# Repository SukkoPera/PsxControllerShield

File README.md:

# PsxControllerShield
PsxControllerShield is an Open Hardware shield for [Arduino](https://www.arduino.cc) that allows it to be interfaced with Sony PlayStation controllers.

### Summary
Interfacing PlayStation controllers with Arduino is easy, since the protocol they use is essentially SPI, but it is a bit tricky at the hardware level, since they are designed to work at 3.6V, while most Arduino work at 5V. A lot of guides out there seem to ignore this fact and say that controllers will work fine even at 5V, but I doubt this will not harm them in the long run. Since overcoming the problem is pretty easy, I designed this shield, which includes level shifters on all data lines and a voltage regulator that will produce much more current than even the most power-greedy controller will need. Just place it on your Arduino, connect the controller and you are good to go!

The shield was designed to be used with [PsxNewLib](https://github.com/SukkoPera/PsxNewLib) on the software side (versions 0.2 and later have a built-in example for that), but it will probably work with other libraries and/or custom code just as well.

The shield also includes three leds that can be freely used by sketches.

### Components and Assembly
Solder all parts in the order you prefer, just keep the controller connector last. This can be found from many Chinese sellers as a spare part. Get one with 90° pins, otherwise the adapter will be pretty awkward to use. The pins will be pretty short, but if you make sure it sits level on the board you should manage to solder it in place, maybe from the top. In order to make the adapter more mechanically solid, you can put some hot glue behind the connector (where the pins are), it won't look pretty but it will do the job.

Note that the controller is powered at 3.3V and the interface signals use the same voltage. Due to the particular circuit used for level shifting (the microcontroller works at 5V), the MOSFETs should really be BSS138.

**NOTE: I recommend using 1k resistors for R1 through R10.** I have checked on a real PsOne and that's the value it uses, so I guess we should do the same. This will be fixed in the next release.

### Compatibility
For the list of supported controllers, please refer to the [PsxNewLib Compatibility List](https://github.com/SukkoPera/PsxNewLib#compatibility-list).

Regarding the supported Arduino boards, this shield should work with all those that work at 5V, such as the *Uno*, *Leonardo* and *Mega*. **It will NOT work with the Due** or other boards that use a 3.3V logic level, and **it will probably destroy them**, so be careful.

If you plan to use the vibration motors you will need to provide them with suitable power, that is 7.6V-9V. This can be done through the barrel jack which should be available on your Arduino board or through the VIN pin. Pay attention **to match the polarity**! Please note that this is untested at the moment (since it is currently not supported by PsxNewLib).

#### Pin Restrictions
The shield uses pin 10 to address the controller and pin 9 for the ACK signal, so these pins cannot be used for any other purpose.

Furthermore, the shield connects the controller data lines to the corresponding pins of the SPI connector (also known as the ICSP connector). Since on some Arduino boards these pins are shared with other digital pins, you won't be able to use them. In particular:
- On the Arduino Uno you cannot use pins 11, 12 and 13.
- On the Arduino Mega you cannot use pins 50, 51 and 52. Pin 53 can be freely used provided that is is kept in OUTPUT mode.

Finally, pins 6, 7 and 8 control the onboard leds (LD3, LD2 and LD1 respectively).

### Releases
If you want to get this board produced, you are recommended to get [the latest release](https://github.com/SukkoPera/PsxControllerShield/releases) rather than the current git version, as the latter might be under development and is not guaranteed to be working.

Every release is accompanied by its Bill Of Materials (BOM) file and any relevant notes about it, which you are recommended to read carefully.

### License
The PsxControllerShield documentation, including the design itself, is copyright &copy; SukkoPera 2020.

PsxControllerShield is Open Hardware licensed under the [CERN OHL v. 1.2](http://ohwr.org/cernohl).

You may redistribute and modify this documentation under the terms of the CERN OHL v.1.2. This documentation is distributed *as is* and WITHOUT ANY EXPRESS OR IMPLIED WARRANTIES whatsoever with respect to its functionality, operability or use, including, without limitation, any implied warranties OF MERCHANTABILITY, SATISFACTORY QUALITY, FITNESS FOR A PARTICULAR PURPOSE or infringement. We expressly disclaim any liability whatsoever for any direct, indirect, consequential, incidental or special damages, including, without limitation, lost revenues, lost profits, losses resulting from business interruption or loss of data, regardless of the form of action or legal theory under which the liability may be asserted, even if advised of the possibility or likelihood of such damages.

A copy of the full license is included in file [LICENSE.pdf](LICENSE.pdf), please refer to it for applicable conditions. In order to properly deal with its terms, please see file [LICENSE_HOWTO.pdf](LICENSE_HOWTO.pdf).

The contact points for information about manufactured Products (see section 4.2) are listed in file [PRODUCT.md](PRODUCT.md).

Any modifications made by Licensees (see section 3.4.b) shall be recorded in file [CHANGES.md](CHANGES.md).

The Documentation Location of the original project is https://github.com/SukkoPera/PsxControllerShield/.

### Support the Project
Since the project is open you are free to get the PCBs made by your preferred manufacturer, however in case you want to support the development, you can order them from PCBWay through this link:

You get my gratitude and cheap, professionally-made and good quality PCBs, I get some credit that will help with this and [other projects](https://www.pcbway.com/project/member/shareproject/?bmbid=41100). You won't even have to worry about the various PCB options, it's all pre-configured for you!

Also, if you still have to register to that site, [you can use this link](https://www.pcbway.com/setinvite.aspx?inviteid=41100) to get some bonus initial credit (and yield me some more).

Again, if you want to use another manufacturer, feel free to, don't feel obligated :). But then you can buy me a coffee if you want:

### Get Help
If you need help or have questions, you can join [the official Telegram group](https://t.me/joinchat/HUHdWBC9J9JnYIrvTYfZmg).

### Thanks
- CuriousInventor for information about the [PlayStation controller protocol](http://store.curiousinventor.com/guides/PS2)
- Nicholas Parks Young for his [Arduino Shield schematic and footprint library for KiCad](https://github.com/Alarm-Siren/arduino-kicad-library)
- Sarang Dumbre for his [3D model of the PlayStation connector](https://grabcad.com/library/ps-connector-female-1)

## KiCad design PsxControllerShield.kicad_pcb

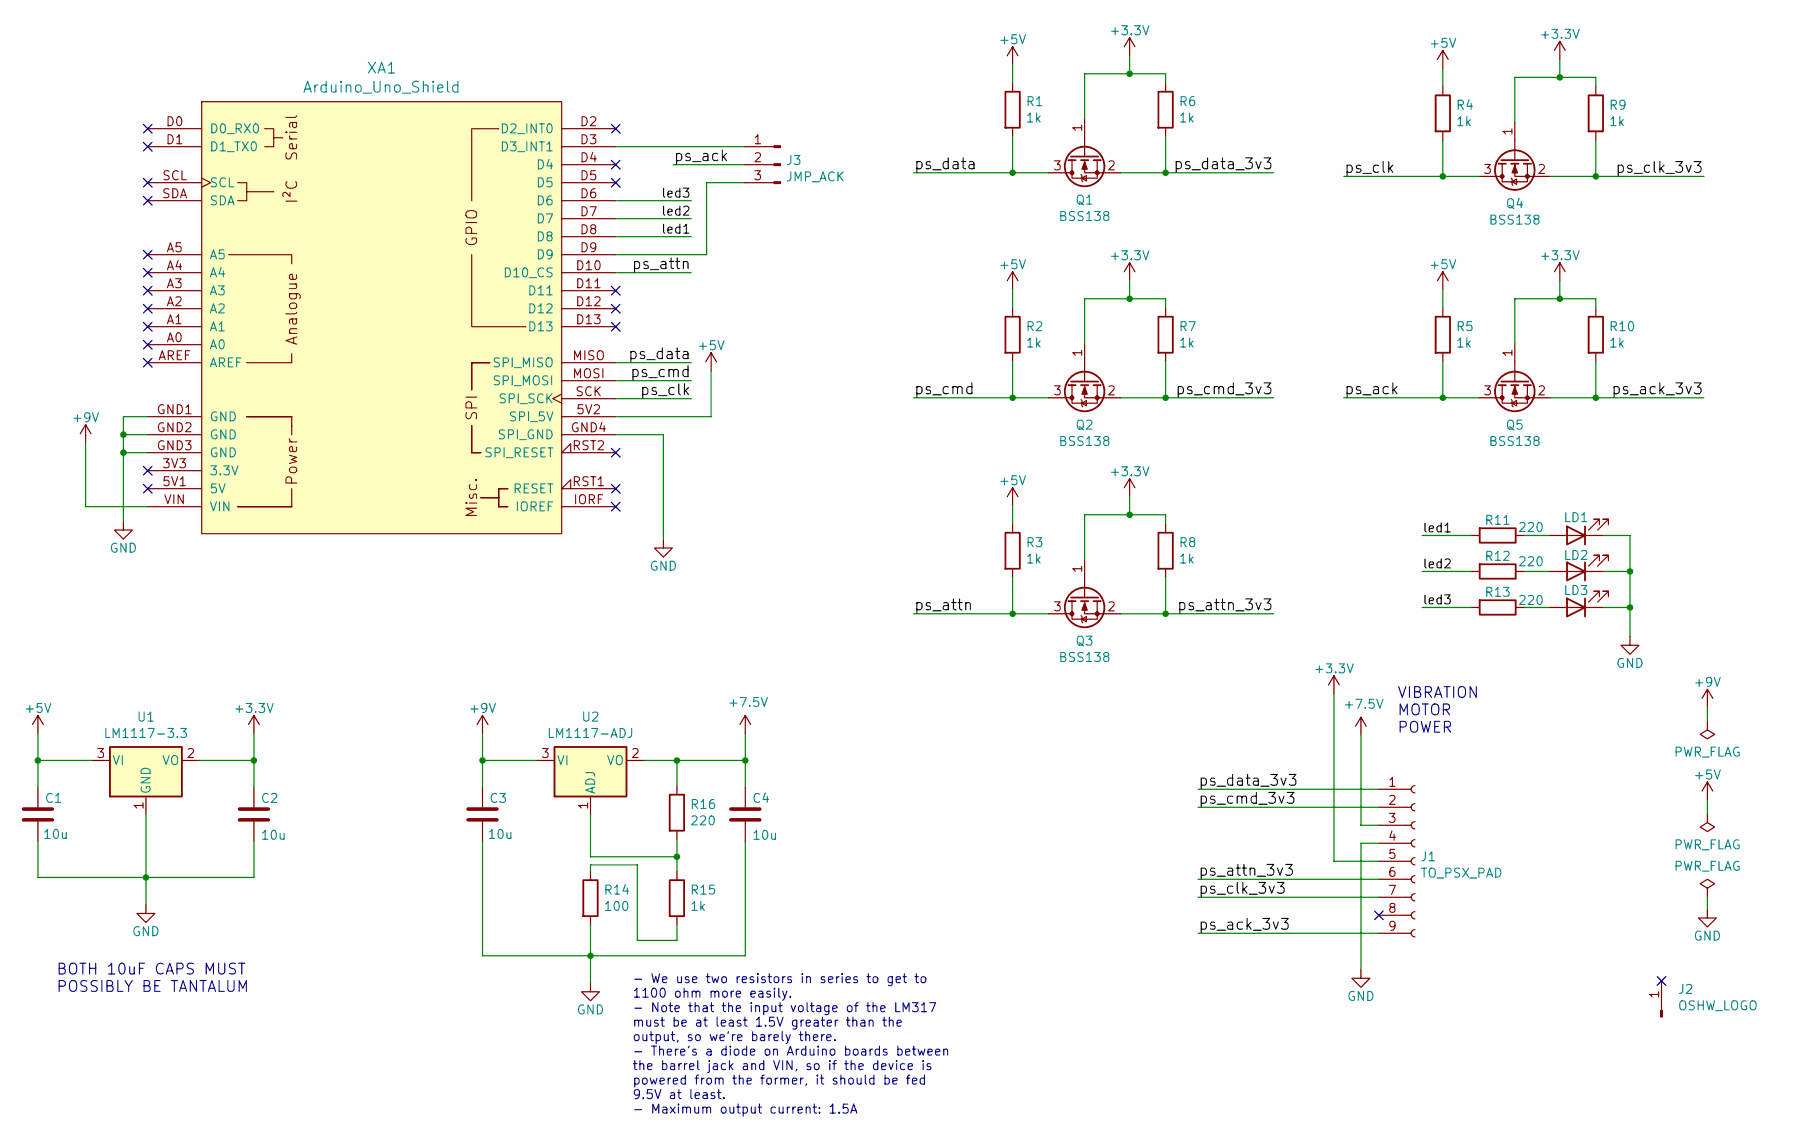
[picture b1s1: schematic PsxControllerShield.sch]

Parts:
C1, C2, C3, C4: 10u; CP_EIA-3528-12_Kemet-T_Pad1.50x2.35mm_HandSolder
J1: TO_PSX_PAD; PSX_Pad_Connector
J2: OSHW_LOGO; OSHW-Logo_7.5x8mm_SilkScreen
J3: JMP_ACK; PinHeader_1x03_P2.54mm_Vertical
LD1, LD2, LD3: LED; LED_0805_2012Metric_Pad1.15x1.40mm_HandSolder
Q1, Q2, Q3, Q4, Q5: BSS138; SOT-23_Handsoldering
R1, R2, R3, R4, R5, R6, R7, R8, R9, R10, R15: 1k; R_0805_2012Metric_Pad1.20x1.40mm_HandSolder
R11, R12, R13, R16: 220; R_0805_2012Metric_Pad1.20x1.40mm_HandSolder
R14: 100; R_0805_2012Metric_Pad1.20x1.40mm_HandSolder
U1: LM1117-3.3; SOT-223-3_TabPin2
U2: LM1117-ADJ; SOT-223-3_TabPin2
XA1: Arduino_Uno_Shield

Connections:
+3V3: C2.2, J1.5, Q1.1 (G), Q2.1 (G), Q3.1 (G), Q4.1 (G), Q5.1 (G), R6.1, R7.1, R8.1, R9.1, R10.1, U1.2 (VO)
+5V: C1.2, R1.1, R2.1, R3.1, R4.1, R5.1, U1.3 (VI), XA1.5V2 (SPI_5V)
+7.5V: C4.2, J1.3, R16.1, U2.2 (VO)
+9V: C3.2, U2.3 (VI), XA1.VIN
/led1: R11.2, XA1.D8
/led2: R12.2, XA1.D7
/led3: R13.2, XA1.D6
/ps_ack: J3.2, Q5.3 (D), R5.2
/ps_ack_3v3: J1.9, Q5.2 (S), R10.2
/ps_attn: Q3.3 (D), R3.2, XA1.D10 (D10_CS)
/ps_attn_3v3: J1.6, Q3.2 (S), R8.2
/ps_clk: Q4.3 (D), R4.2, XA1.SCK (SPI_SCK)
/ps_clk_3v3: J1.7, Q4.2 (S), R9.2
/ps_cmd: Q2.3 (D), R2.2, XA1.MOSI (SPI_MOSI)
/ps_cmd_3v3: J1.2, Q2.2 (S), R7.2
/ps_data: Q1.3 (D), R1.2, XA1.MISO (SPI_MISO)
/ps_data_3v3: J1.1, Q1.2 (S), R6.2
GND: C1.1, C2.1, C3.1, C4.1, J1.4, LD1.1 (K), LD2.1 (K), LD3.1 (K), R14.2, U1.1 (GND), XA1.GND1 (GND), XA1.GND2 (GND), XA1.GND3 (GND), XA1.GND4 (SPI_GND)
unnamed: J3.1, XA1.D3 (D3_INT1)
unnamed: J3.3, XA1.D9
unnamed: LD1.2 (A), R11.1
unnamed: LD2.2 (A), R12.1
unnamed: LD3.2 (A), R13.1
unnamed: R14.1, R15.2
unnamed: R15.1, R16.2, U2.1 (ADJ)

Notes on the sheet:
VIBRATION MOTOR POWER
BOTH 10uF CAPS MUST POSSIBLY BE TANTALUM
- We use two resistors in series to get to 1100 ohm more easily. - Note that the input voltage of the LM317 must be at least 1.5V greater than the output, so we're barely there. - There's a diode on Arduino boards between the barrel jack and VIN, so if the device is powered from the former, it shou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

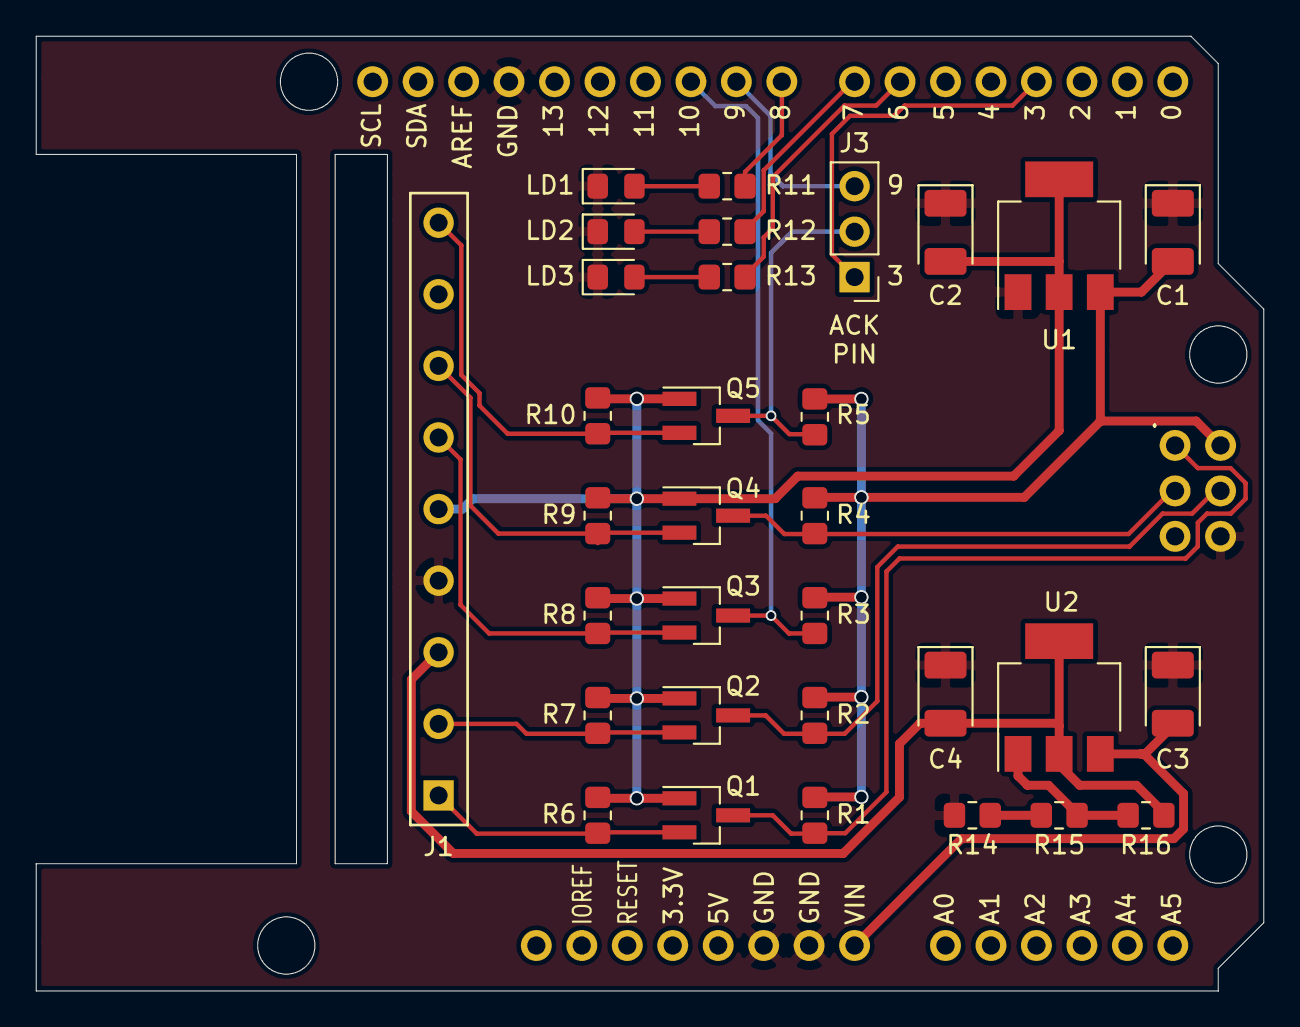
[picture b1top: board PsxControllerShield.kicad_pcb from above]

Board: 2 copper layers, 68.6 x 53.3 mm, 34 parts (1 on the bottom side), 25 nets.

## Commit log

2019-12-27 Work in progress
2020-01-03 Ready for protoypes!
2020-02-17 Add license
2020-02-29 Mention PsxNewLib releases working with this shield
2020-02-29 Update version numbers for first release
2020-02-29 Add renders
2020-02-29 Add schematics PDF
2020-02-29 Add credits for shield footprint/library
2020-02-29 Fix typos
2020-02-29 Add link to PSX connector 3D model
2020-02-29 Add Arduino shield library and footprint How did we lose this???
2021-03-26 Remove fp-info-cache
2021-03-26 Add note on pull-up resistors
2021-04-29 Ready for V2 (probably) Changes wrt V1: - Added 7.5V regulator for motors (I still think they're probably fine with 9V, but we want to be 100% rigorous with this board) - Move PSX connector towards b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
2021-07-10 Use larger footprint for tantalums
2021-07-10 Move tracks around
2021-07-10 Add ability to select ACK pin between 3 and 9
2021-07-11 Align some stuff

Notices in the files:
PsxControllerShield.kicad_pcb:
Licensed under CERN OHL v.1.2
